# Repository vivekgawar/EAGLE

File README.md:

# EAGLE
PCB Design, Schematics and Layout for the boards with Problem Statements:
1) Basic LED circuit
2) 555 Timer application circuit
3) Interfacing LED and Push button to ATMega32
4) Interfacing MAX232 to ATMega32
5) Interfacing 4x4 Keypad with ATMega32
6) Rotating toy with rhythmic LED pattern and voice or musical audio chip-on-board(CoB)
For the above problem statements, a schematic and the layout must be completed.

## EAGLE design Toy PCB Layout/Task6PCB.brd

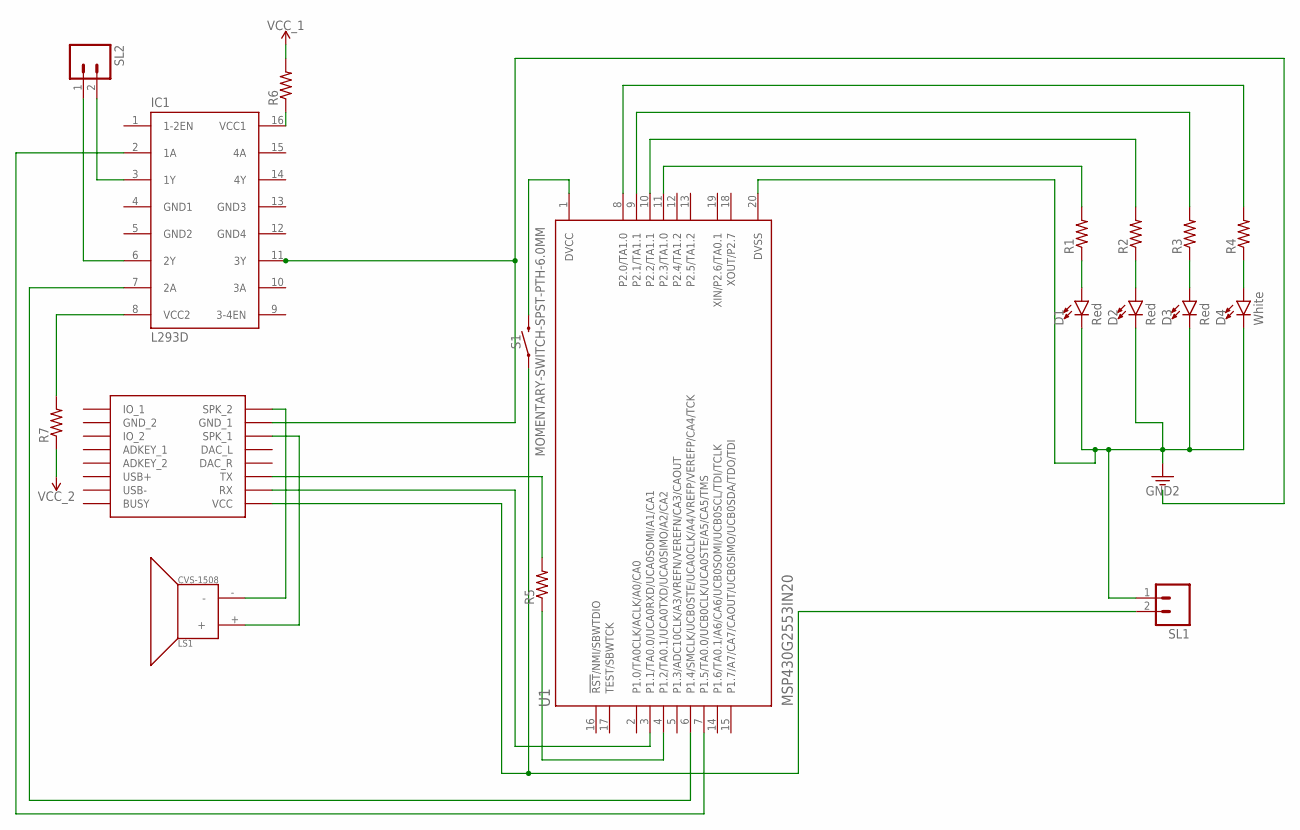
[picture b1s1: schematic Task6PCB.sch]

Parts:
D1, D2, D3: Red; LED-0603
D4: White; LED-1206
IC1: L293D; DIL16
LS1: CVS-1508; CVS-1508_PCBSPKR
R1, R2, R3, R4, R5, R6, R7: R-US_0204/7; 0204/7
S1: MOMENTARY-SWITCH-SPST-PTH-6.0MM; TACTILE_SWITCH_PTH_6.0MM
SL1, SL2: M02; 02P
U1: MSP430G2553IN20; DIP794W45P254L2540H508Q20
U$1: DFPLAYER

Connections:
3.3V: D1.C, D2.C, D3.C, D4.C, SL1.1, U1.20 (DVSS)
GND1: IC1.4 (GND1)
GND2: IC1.5 (GND2)
GND3: IC1.13 (GND3)
GND4: IC1.12 (GND4)
unnamed: R5.1, U1.4 (P1.2/TA0.1/UCA0TXD/UCA0SIMO/A2/CA2)
unnamed: R2.2, U1.10 (P2.2/TA1.1)
unnamed: IC1.7 (2A), U1.6 (P1.4/SMCLK/UCB0STE/UCA0CLK/A4/VREFP/VER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)
unnamed: IC1.8 (VCC2), R7.2
unnamed: D1.A, R1.1
unnamed: D4.A, R4.1
unnamed: R3.2, U1.9 (P2.1/TA1.1)
unnamed: D3.A, R3.1
unnamed: R4.2, U1.8 (P2.0/TA1.0)
unnamed: D2.A, R2.1
unnamed: U1.3 (P1.1/TA0.0/UCA0RXD/UCA0SOMI/A1/CA1), U$1.RX
unnamed: R5.2, U$1.TX
unnamed: R1.2, U1.11 (P2.3/TA1.0)
unnamed: LS1.+, U$1.SPK1 (SPK_1)
unnamed: LS1.-, U$1.SPK2 (SPK_2)
unnamed: IC1.16 (VCC1), R6.1
unnamed: S1.1, SL1.2, U$1.VCC
unnamed: IC1.11 (3Y), U$1.GND_1
unnamed: IC1.3 (1Y), SL2.2
unnamed: IC1.6 (2Y), SL2.1
unnamed: S1.3 (2), U1.1 (DVCC)
unnamed: IC1.2 (1A), U1.7 (P1.5/TA0.0/UCB0CLK/UCA0STE/A5/CA5/TMS)
VCC_1: R6.2
VCC_2: R7.1

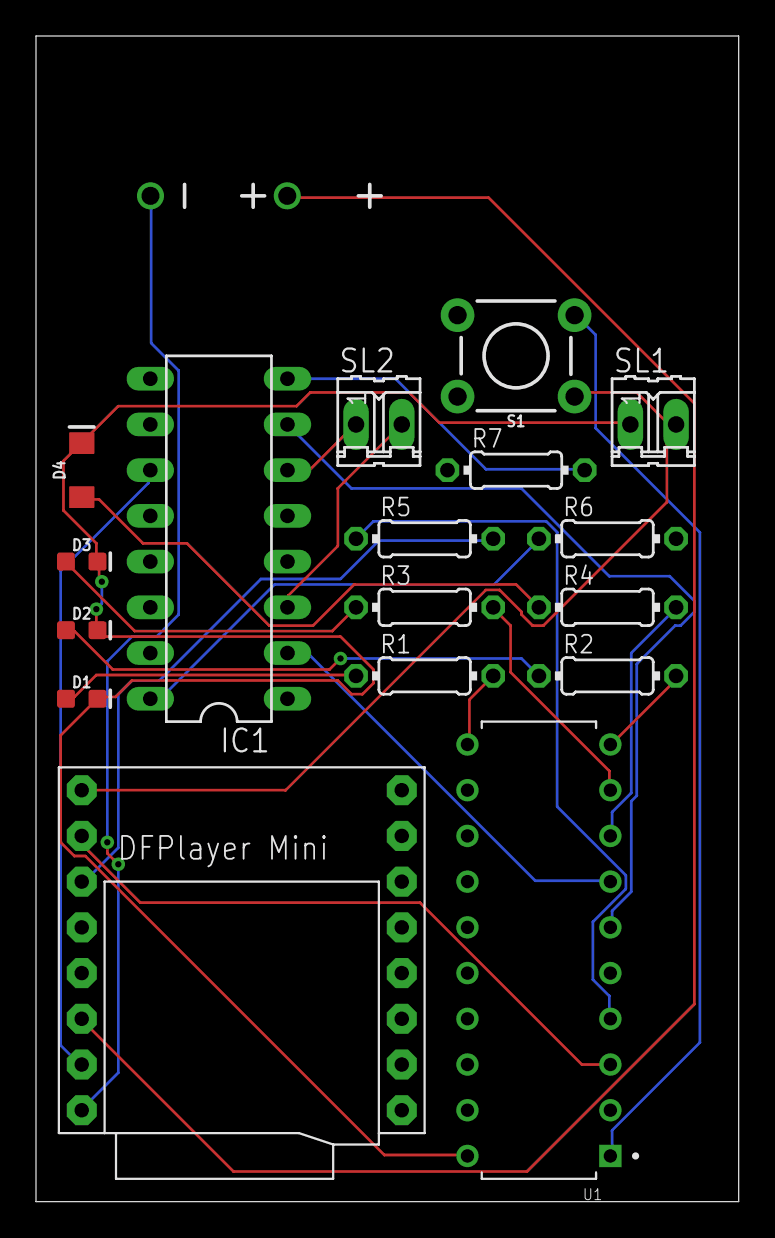
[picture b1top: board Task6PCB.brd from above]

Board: 2 copper layers, 39.0 x 64.8 mm, 18 parts (0 on the bottom side), 23 nets.

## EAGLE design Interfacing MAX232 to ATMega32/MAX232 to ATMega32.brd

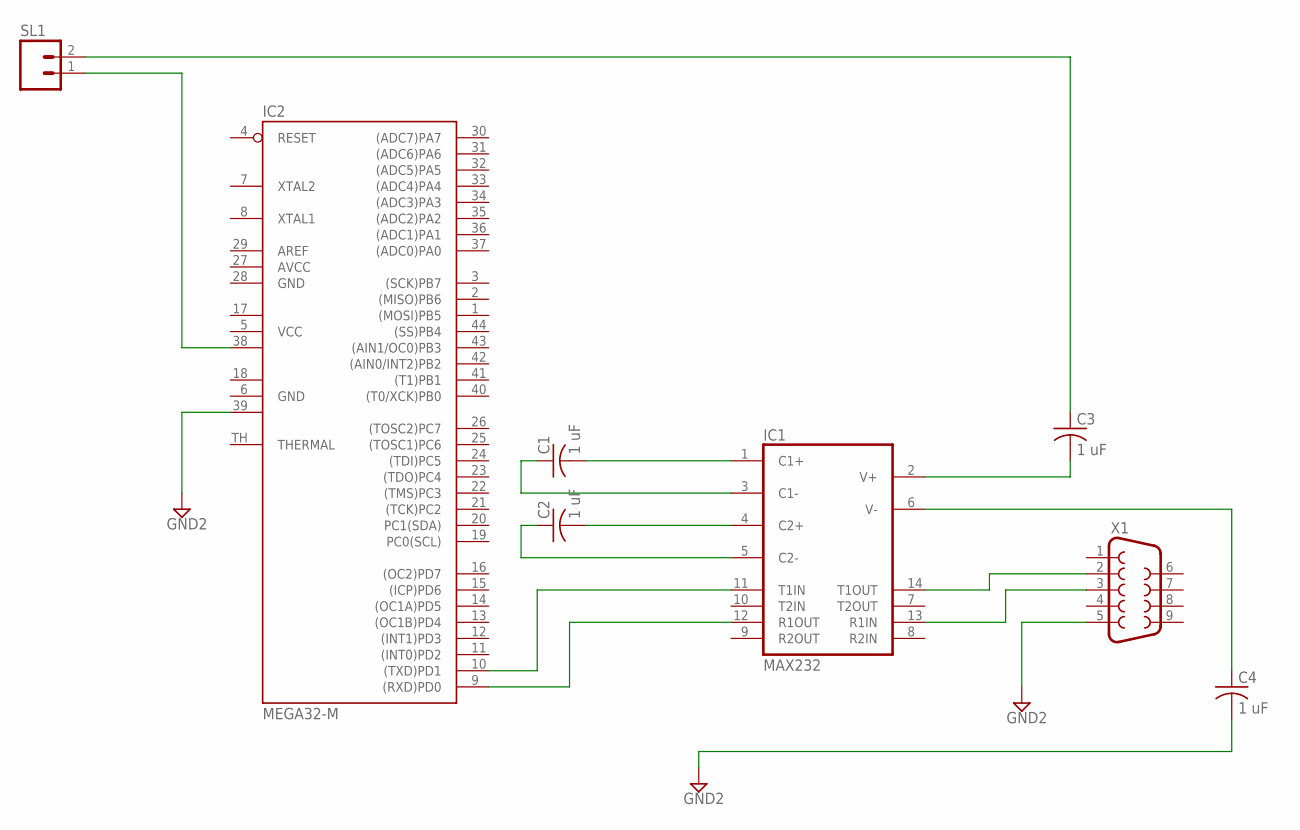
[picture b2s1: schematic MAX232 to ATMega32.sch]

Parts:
C1, C2, C3, C4: 1 uF; C025-025X050
IC1: MAX232; DIL16
IC2: MEGA32-M; MLF44-TH
SL1: M02; 02P
X1: F09VB

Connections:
AVCC: IC2.27 (AVCC)
GND: IC1.15 (GND), IC2.6 (GND), IC2.28 (GND)
GND1: IC2.18 (GND1)
GND2: C4.2, IC2.39 (GND2), X1.5
unnamed: IC1.14 (T1OUT), X1.2
unnamed: IC1.13 (R1IN), X1.3
unnamed: IC1.11 (T1IN), IC2.10 ((TXD)PD1)
unnamed: IC1.12 (R1OUT), IC2.9 ((RXD)PD0)
unnamed: C3.2, IC1.2 (V+)
unnamed: C4.1, IC1.6 (V-)
unnamed: C1.2, IC1.1 (C1+)
unnamed: C1.1, IC1.3 (C1-)
unnamed: C2.2, IC1.4 (C2+)
unnamed: C2.1, IC1.5 (C2-)
unnamed: C3.1, SL1.2
unnamed: IC2.38 (VCC2), SL1.1
VCC: IC1.16 (VCC), IC2.5 (VCC)
VCC1: IC2.17 (VCC1)

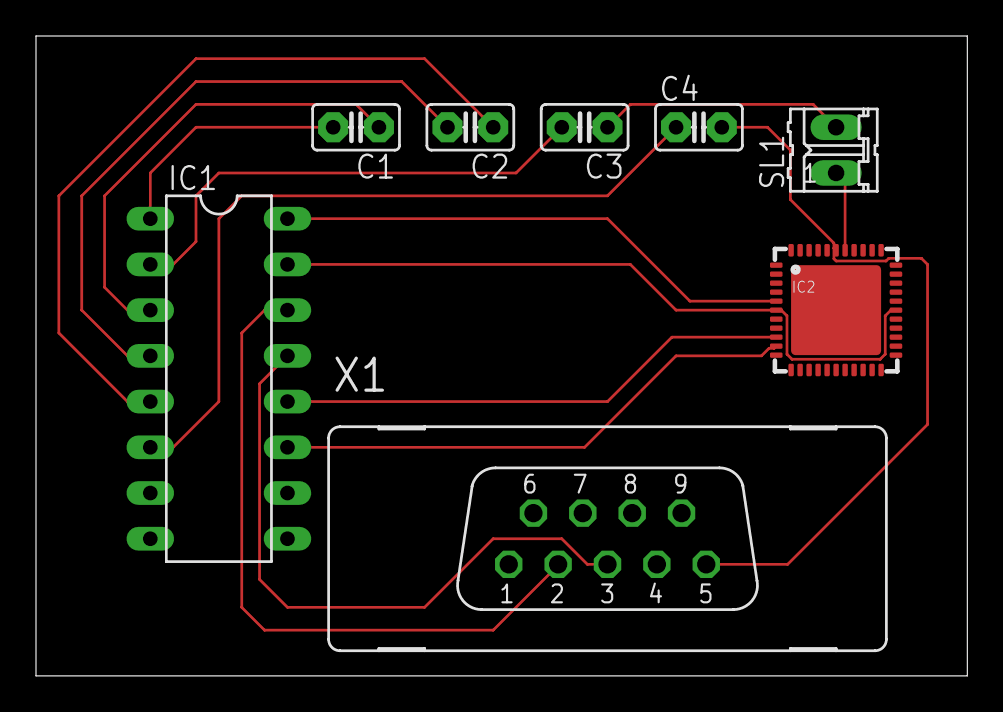
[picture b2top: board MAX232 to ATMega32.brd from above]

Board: 2 copper layers, 51.7 x 35.5 mm, 8 parts (0 on the bottom side), 15 nets.

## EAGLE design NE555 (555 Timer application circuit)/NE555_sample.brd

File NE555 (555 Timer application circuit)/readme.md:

NE555 Timer Application Circuit

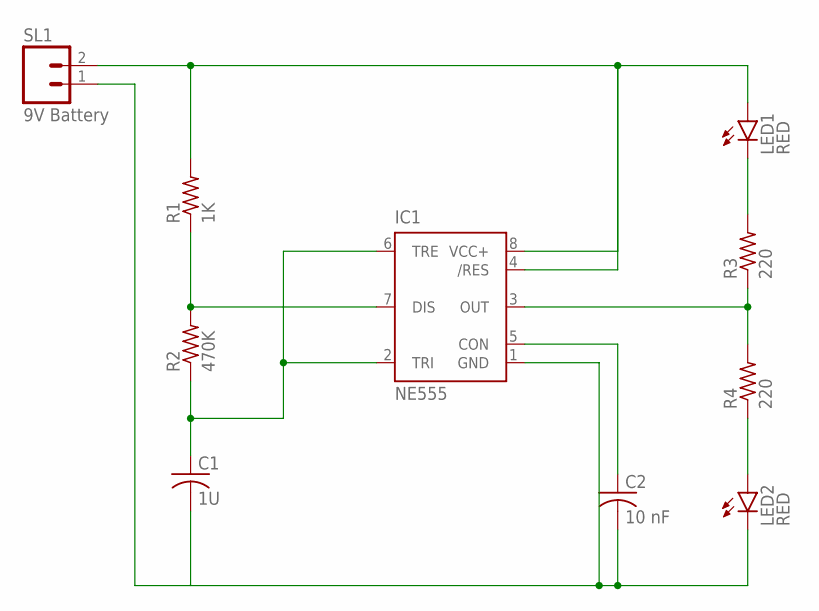
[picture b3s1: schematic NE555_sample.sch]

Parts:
C1: 1U; C0805
C2: 10 nF; C0805
IC1: NE555; DIL-08
LED1, LED2: RED; CHIPLED_0805
R1: 1K; R0805
R2: 470K; R0805
R3, R4: 220; R0805
SL1: 9V Battery; 02P

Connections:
unnamed: IC1.4 (/RES), IC1.8 (VCC+), LED1.A, R1.2, SL1.2
unnamed: LED1.C, R3.2
unnamed: IC1.3 (OUT), R3.1, R4.2
unnamed: LED2.A, R4.1
unnamed: C1.2, C2.2, IC1.1 (GND), LED2.C, SL1.1
unnamed: C1.1, IC1.2 (TRI), IC1.6 (TRE), R2.1
unnamed: IC1.7 (DIS), R1.1, R2.2
unnamed: C2.1, IC1.5 (CON)

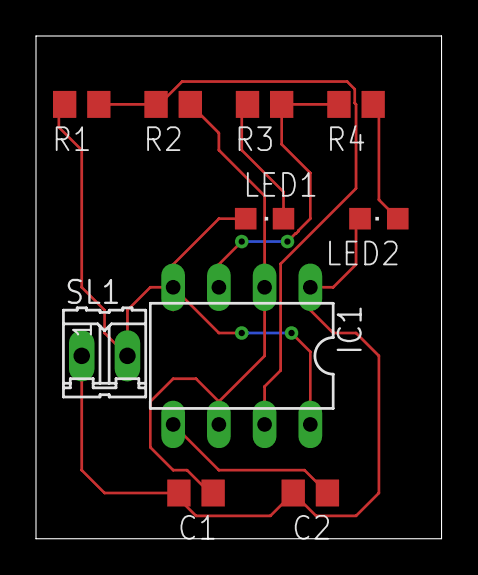
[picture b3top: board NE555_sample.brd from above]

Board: 2 copper layers, 22.5 x 27.9 mm, 10 parts (0 on the bottom side), 8 nets.

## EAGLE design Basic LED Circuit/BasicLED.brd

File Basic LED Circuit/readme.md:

A simple LED Circuit with EAGLE

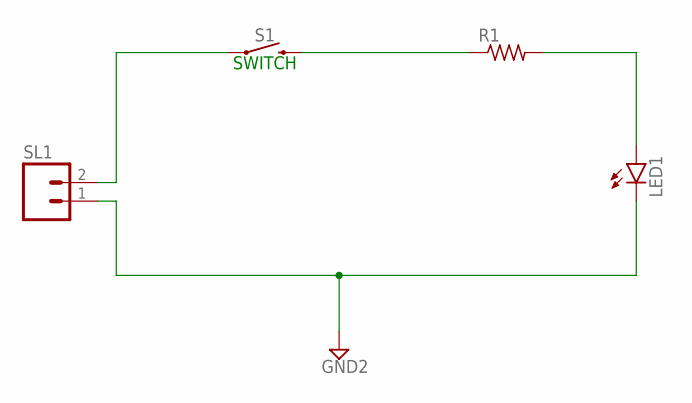
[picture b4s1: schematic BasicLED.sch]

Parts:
LED1: LEDCHIP-LED0805; CHIP-LED0805
R1: R-US_R0805; R0805
S1: SWITCH; TACTILE_SWITCH_SMD_4.5MM
SL1: M02; 02P

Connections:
GND2: LED1.C, SL1.1
unnamed: S1.2 (1), S1.3 (1), SL1.2
unnamed: R1.1, S1.1 (2), S1.4 (2)
unnamed: LED1.A, R1.2

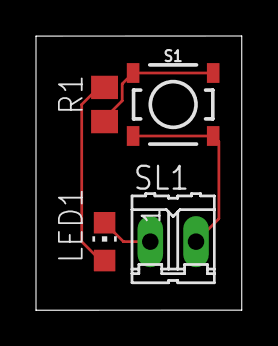
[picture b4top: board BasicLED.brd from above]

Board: 2 copper layers, 11.4 x 15.2 mm, 4 parts (0 on the bottom side), 4 nets.

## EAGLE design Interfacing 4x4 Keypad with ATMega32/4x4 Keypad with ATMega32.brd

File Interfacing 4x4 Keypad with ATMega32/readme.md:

Interfacing 4x4 Keypad with ATMega32

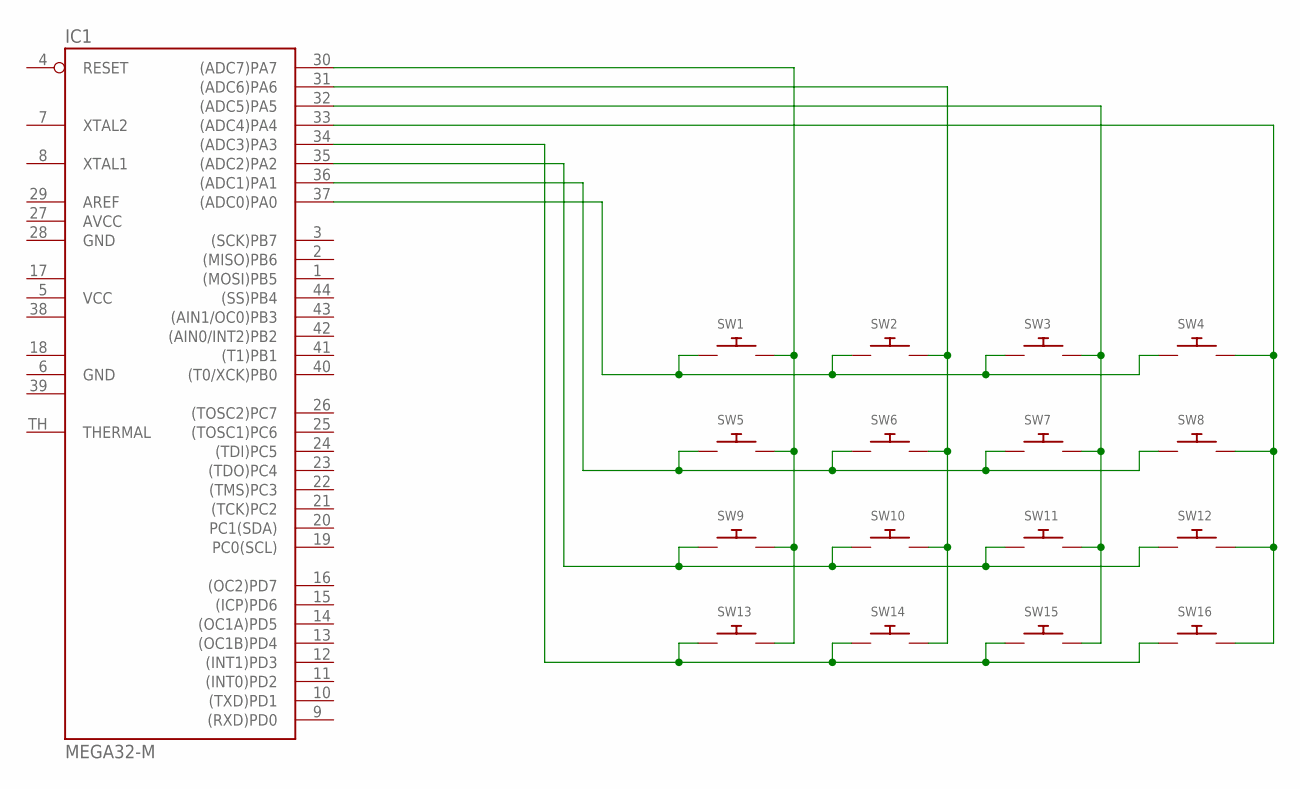
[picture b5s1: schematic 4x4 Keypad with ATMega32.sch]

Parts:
IC1: MEGA32-M; MLF44-TH
SW1, SW2, SW3, SW4, SW5, SW6, SW7, SW8, SW9, SW10, SW11, SW12, SW13, SW14, SW15, SW16: SWITCH_PUSHBUTTONC&K_KSS; BTN_CK_KSS

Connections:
AVCC: IC1.27 (AVCC)
GND: IC1.6 (GND), IC1.28 (GND)
GND1: IC1.18 (GND1)
GND2: IC1.39 (GND2)
unnamed: IC1.37 ((ADC0)PA0), SW1.P$1, SW2.P$1, SW3.P$1, SW4.P$1
unnamed: IC1.33 ((ADC4)PA4), SW4.P$2, SW8.P$2, SW12.P$2, SW16.P$2
unnamed: IC1.32 ((ADC5)PA5), SW3.P$2, SW7.P$2, SW11.P$2, SW15.P$2
unnamed: IC1.35 ((ADC2)PA2), SW9.P$1, SW10.P$1, SW11.P$1, SW12.P$1
unnamed: IC1.34 ((ADC3)PA3), SW13.P$1, SW14.P$1, SW15.P$1, SW16.P$1
unnamed: IC1.31 ((ADC6)PA6), SW2.P$2, SW6.P$2, SW10.P$2, SW14.P$2
unnamed: IC1.30 ((ADC7)PA7), SW1.P$2, SW5.P$2, SW9.P$2, SW13.P$2
unnamed: IC1.36 ((ADC1)PA1), SW5.P$1, SW6.P$1, SW7.P$1, SW8.P$1
VCC: IC1.5 (VCC)
VCC1: IC1.17 (VCC1)
VCC2: IC1.38 (VCC2)

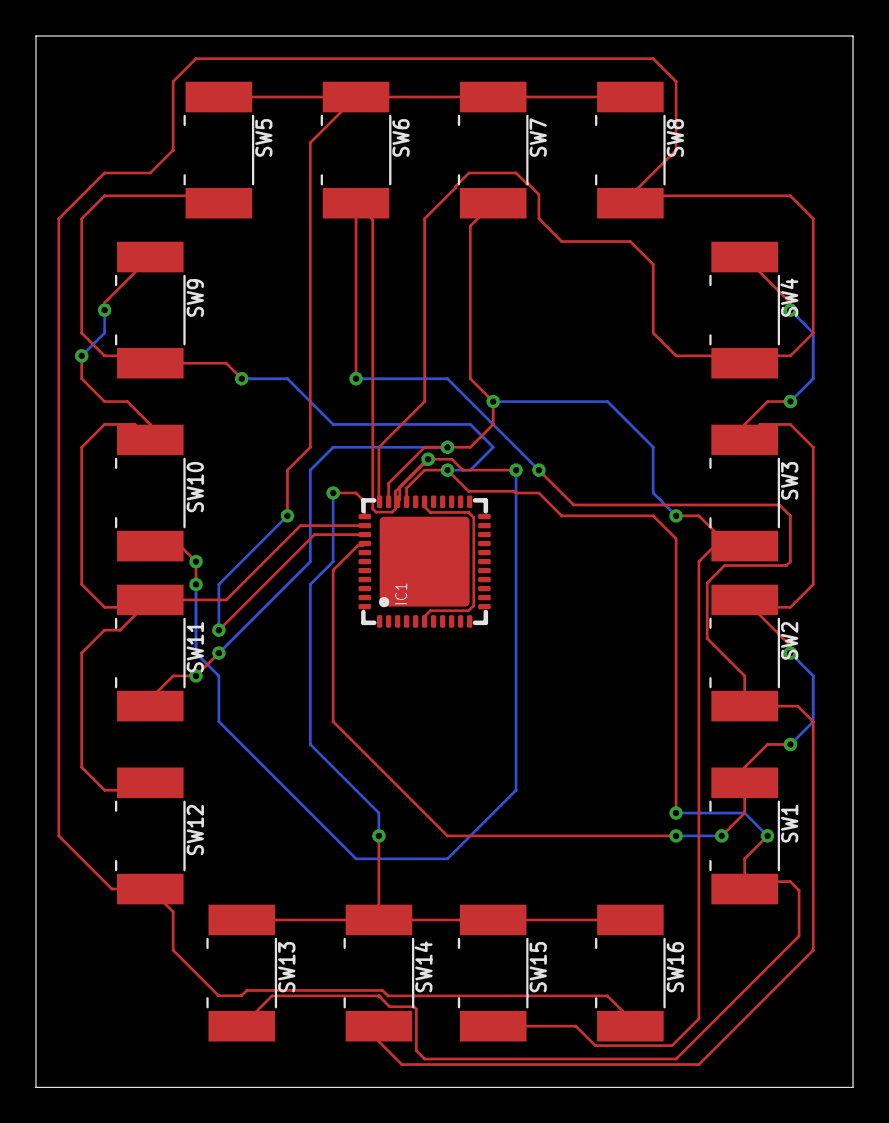
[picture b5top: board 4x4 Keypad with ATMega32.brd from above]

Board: 2 copper layers, 45.4 x 58.4 mm, 17 parts (0 on the bottom side), 9 nets.

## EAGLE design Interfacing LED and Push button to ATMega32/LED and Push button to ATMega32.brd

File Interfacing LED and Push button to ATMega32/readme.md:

Interfacing LED and Push button to ATMega32

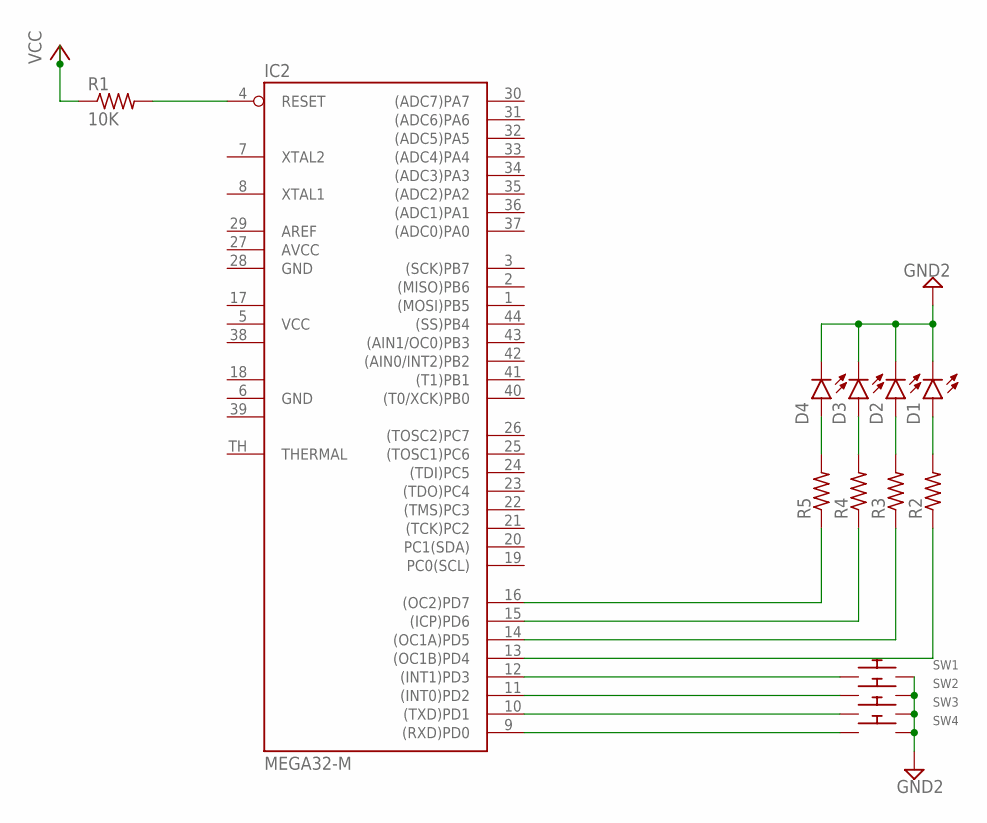
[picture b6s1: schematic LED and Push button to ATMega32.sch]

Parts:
D1, D2, D3, D4: LEDCHIPLED_0805; CHIPLED_0805
IC2: MEGA32-M; MLF44-TH
R1: 10K; R0805
R2, R3, R4, R5: 330R; R0805
SW1, SW2, SW3, SW4: SWITCH_PUSHBUTTONC&K_KSS; BTN_CK_KSS

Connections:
AVCC: IC2.27 (AVCC)
GND: IC2.6 (GND), IC2.28 (GND)
GND1: IC2.18 (GND1)
GND2: D1.C, D2.C, D3.C, D4.C, IC2.39 (GND2), SW1.P$2, SW2.P$2, SW3.P$2, SW4.P$2
unnamed: IC2.9 ((RXD)PD0), SW4.P$1
unnamed: IC2.10 ((TXD)PD1), SW3.P$1
unnamed: IC2.11 ((INT0)PD2), SW2.P$1
unnamed: IC2.12 ((INT1)PD3), SW1.P$1
unnamed: IC2.13 ((OC1B)PD4), R2.1
unnamed: IC2.14 ((OC1A)PD5), R3.1
unnamed: IC2.15 ((ICP)PD6), R4.1
unnamed: IC2.16 ((OC2)PD7), R5.1
unnamed: D4.A, R5.2
unnamed: D3.A, R4.2
unnamed: D2.A, R3.2
unnamed: D1.A, R2.2
unnamed: IC2.4 (RESET), R1.2
VCC: IC2.5 (VCC), R1.1
VCC1: IC2.17 (VCC1)
VCC2: IC2.38 (VCC2)

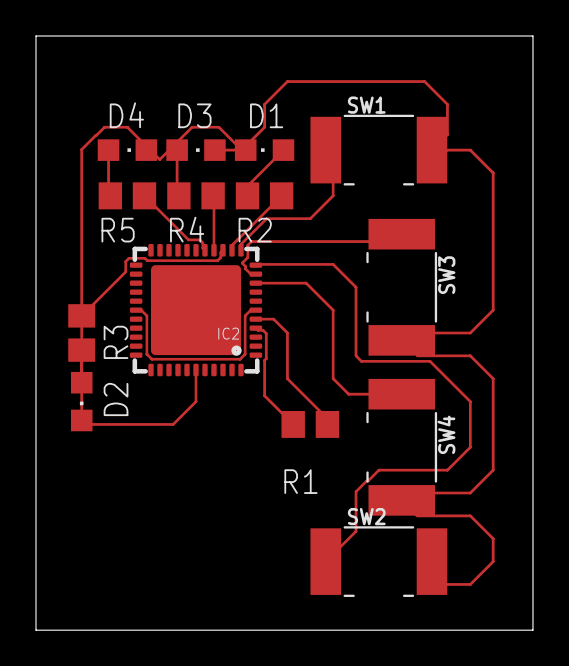
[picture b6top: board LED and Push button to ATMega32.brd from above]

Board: 2 copper layers, 27.6 x 33.0 mm, 14 parts (0 on the bottom side), 16 nets.

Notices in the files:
parts and their libraries:
SparkFun-Switches: Licensing: Creative Commons ShareAlike 4.0 International - https://creativecommons.org/licenses/by-sa/4.0
